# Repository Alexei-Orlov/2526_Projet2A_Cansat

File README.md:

# 🛰️ CanSat 2025-2026
   
> **ENSEA's CanSat team project for the 2025–2026 C'Space edition**

We are a team of second-year engineering students at ENSEA taking part in the 2025–2026 edition of the CanSat competition. CanSat competitions challenge teams to design, build and launch a can-sized (33 cl) satellite that carries out scientific or engineering missions during its descent.

This year's missions are listed below:

- **Main Mission (Mandatory)**
   - **Mission 1: Deployment and Landing**
       - **Integration**: The CanSat must be equipped with a parachute stowed inside the device, designed to deploy during flight.
       - **Deployment**: The CanSat must successfully deploy its parachute at an altitude between 75 and 90 meters.

- **Secondary Missions (Optional)**
    - **Mission 2: Downsizing**
    **Reducing** the CanSat to a 33 cl format doubles the team's score on the technical section.

    - **Mission 3: Ground Study**
    Conduct a study of a topographical feature during the flight.

    - **Mission 4: Onboard Camera**
    Record a video of the parachute deployment or of the CanSat's landing.

- **Bonus Mission**
    - During the descent or after landing, the CanSat may perform an additional mission. Its evaluation is at the jury's discretion, and it must be validated by the controllers during RCE1 to ensure compliance with the rules.

And finally, here is the list of team members and their roles:

| Name | Role |
|------|------|
| Alexeï DOUILLARD | 3D Modeling, Satellite integration, PCB |
| Juan Pablo BARONA CIFUENTES | Embedded systems, firmware |
| Ted KOYAZANDE | Ground Station, Communications |
| Amr TAOUIS | PCB Design and testing |
| Abdelmoughit HAJJI LAAMOURI | Code |

---

## 📋 Table of Contents

- [Objectives](#-objectives)
- [Project Structure](#-project-structure)
- [Development](#-development)
  - [Block diagram of the solution](#-block-diagram-of-the-solution)
  - [Used components description](#-used-components-description)
  - [Electronic design](#-electronic-design)
  - [Mechanical design](#%EF%B8%8F-mechanical-design)
  - [RTOS software architecture](#-rtos-software-architecture)
  - [Data acquisition & routing flow](#-data-acquisition--routing-flow)
  - [Communications & software architecture](#-communications--software-architecture)
  - [Ground Station](#-ground-station-mission-control-center)
  - [Telemetry analysis & 3D terrain reconstruction](#-telemetry-analysis--3d-terrain-reconstruction)
  - [Wind tunnel](#-wind-tunnel)
  - [Drone](#%EF%B8%8F-drone)
- [Resources and useful links](#-resources-and-useful-links)
- [Future plans](#-future-plans)

---

## 📋 Objectives

Based on the missions we chose to fulfill among those listed above, we defined the following objectives.

- **Main Mission (Mandatory)**
  - Design a kirigami-inspired drogue chute that also acts as a protective cap on the CanSat and is used to extract the main parachute. The drogue chute is released by a string and an elastic band tied to a servomotor; the whole mechanism is tested in a homemade wind tunnel.

- **Secondary Missions**
  - **Mission 2: Downsizing**
    - Fit everything within the 330 mL / 350 g limits, using a 6-layer PCB and a very lightweight parachute.

  - **Mission 3: Ground study**
    - **Plan A** (currently active):
      Use a 100 m time-of-flight (ToF) LiDAR to map the ground.
      Induce a rotation thanks to a helicoidal-shaped can, so the beam sweeps the terrain in a spiral as the CanSat falls.
      Georeference each measured point using an Inertial Measurement Unit (IMU), a barometer and a GNSS receiver. The wind tunnel is also used to validate that the can shape actually spins.
    - **Plan B**:
      Use a high-resolution camera to film the whole descent and build a topographical map with AI-based reconstruction after the mission.
  - **Mission 4: Onboard Camera**
    - Record the landing using a small self-contained mini camera.
- **Bonus Mission**
  - Stream part of the recorded data to the ground station during the descent, within the transmission rate of our LoRa module.

## 📁 Project Structure

```
2526_Projet2A_Cansat/
│
├── 📖 README.md                     # This file — project overview
├── 📖 README_GUI.md                 # Ground segment & data pipeline documentation
├── 📄 logs.md                       # Session-by-session work log
│
├── 💻 Firmware/satellite_telemetry/
│   ├── Cansat_V1/                   # STM32CubeIDE project — current flight firmware
│   ├── Cansat_V3/                   # Next firmware iteration (in progress)
│   ├── GUI/                         # Ground station application (Raspberry Pi 5, PyQt5)
│   └── Analysis_Tools/              # Legacy analysis scripts (superseded by 3D/)
│
├── 📂 3D/                           # Post-flight analysis & LIDAR point cloud pipeline
│   ├── cloudPoints.py               # 3D terrain point cloud (main tool)
│   ├── distanceDistribution.py      # LIDAR range histogram
│   ├── generate_sample_data.py      # Synthetic test data generator
│   ├── lidar_common.py              # Shared loading / cleaning / georeferencing
│   ├── COMMANDES.txt                # Full CLI reference
│   └── Analysis_Tools/              # Telemetry dashboards & physics analyses
│
├── ⚡ Hardware/
│   ├── PCB/                         # KiCad projects: Mainboard V1/V2/V3, HMI, custom libraries
│   └── 3D_Modeling/                 # Mechanical schematic & STL exports
│
├── 📂 backup data cansat/           # Real SD-card datasets from field tests
├── 🖼️ IMG/                          # Pictures used by the documentation
├── 📂 Documents/                    # SCAE documents, pictures, definition dossier
├── 📂 Reports/                      # Project reports (PDF)
└── 📂 Wind turbine/                 # Wind tunnel documentation & CFD attempt
```

## 🔧 Development

The development section is divided into four parts:
- Block diagram
- Explanation of the components
- Technical sections
- Software used

First, here is the block diagram of the solution, which shows how the project is organized.

### 💡 Block diagram of the solution

<div align="center">
  <br><br>
  
</div>

### 🔗 Used components description

All the blocks shown above are implemented with the components listed below.

| Component | Reference | Description | Justification |
| :--- | :--- | :--- | :--- |
| **LoRa Module** | SX1276 | The SX1276/77/78/79 transceivers feature the LoRa™ long-range modem, providing ultra-long-range spread-spectrum communication and high interference immunity while minimizing current consumption. | Long-range communication was required with a solid, reliable interface; it was also recommended by last year's CanSat team from the school. Mounted on the mainboard PCB. |
| **LiDAR Altimeter** | LW20/C | A compact, IP67-rated laser altimeter from LightWare. It provides high-precision distance measurements up to 100 meters using time-of-flight technology, and supports multiple returns. | Enables accurate terrain mapping for the ground study mission. |
| **Microcontroller (MCU)** | STM32G431CBU6 | A 32-bit ARM Cortex-M4 microcontroller by STMicroelectronics, featuring mixed-signal capabilities, high-speed processing (170 MHz) and hardware mathematical accelerators (CORDIC/FMAC). | High processing speed is required for sensor fusion and real-time control loops, handling data faster and more efficiently than typical beginner boards. |
| **Barometer** | BMP581 | A high-precision absolute barometric pressure sensor designed for mobile applications, offering low noise and low power consumption. | Determines altitude and vertical velocity (descent rate). It is critical for triggering parachute deployment based on pressure changes. Also recommended by last year's team. |
| **IMU (Inertial Measurement Unit)** | BNO055 | A 9-axis System-in-Package integrating a triaxial 14-bit accelerometer, a triaxial 16-bit gyroscope (±2000 °/s) and a triaxial geomagnetic sensor, with a dedicated microcontroller running the sensor fusion. | Provides orientation data (Euler angles, quaternions) directly. The onboard sensor fusion offloads complex math from the main MCU, ensuring accurate attitude estimation. |
| **GNSS Module** | SAM-M10Q | A patch-antenna module from u-blox featuring the M10 standard-precision GNSS platform. It supports concurrent reception of four GNSS constellations (GPS, GLONASS, Galileo and BeiDou). | Required to track the CanSat's trajectory and lateral drift. Concurrent reception ensures a faster time-to-first-fix and better positioning accuracy, and it provides a redundant altitude source. |
| **Voltage Regulator (LDO)** | LDO40LPU33RY | A high-precision, low-dropout voltage regulator from STMicroelectronics providing a stable output with low quiescent current and low noise. | Provides a clean, stable 3.3 V rail to the sensitive electronics (MCU and sensors), filtering out noise coming from the main power rail. |
| **Local Storage** | MicroSD card + Molex 473092651 | A standard high-capacity non-volatile flash storage card interfaced over SPI through the Molex 473092651 card reader. | Stores the full sensor telemetry and the high-rate LiDAR stream with timestamps. This is the data recovered post-flight for analysis and terrain reconstruction. |
| **Single-Board Computer** | Raspberry Pi 5 | A low-cost, credit-card-sized computer running a Linux-based operating system. | Hosts the ground station: it processes the incoming telemetry stream, runs the graphical user interface (GUI) for data visualization and stores the mission logs. |
| **Battery** | 2-cell LiPo (7.4 V), 2 × 500 mAh | A lithium-polymer rechargeable battery pack of two cells in series, providing a nominal 7.4 V and high discharge capability. | The 7.4 V output matches the input range of the voltage regulators, providing enough headroom to maintain stable power throughout the mission. |
| **Buck Converter** | LMR51625 | A wide-input synchronous buck converter from Texas Instruments, designed to step high input voltages down to logic levels with high efficiency in a compact footprint. | Steps the 7.4 V battery voltage down to 5 V efficiently. Unlike a linear regulator, this switching regulator minimizes heat generation and power loss. |
| **JST Connectors** | JST SH vertical | Small board-to-wire connectors, used in 3- to 7-pin variants. Thanks JST for the samples! | All external modules are connected through JST SH connectors — a good compromise between compactness and ease of use. |
| **Camera** | Drone camera | HD camera module salvaged from a drone, with a 2.4 GHz receiver and an SD card reader, powered by a separate 500 mAh 3.4 V battery. | We found two very similar HD cameras from cheap drones; one only works through a Wi-Fi app while the other one is controllable via UART. |

### 🔌 Electronic design
#### Mainboard PCB
The electronic architecture of the Vortex project is based on a reverse-engineering process. By analyzing last year's project — and more precisely last year's PCB — we identified the key points of the design and the components that needed to change. Based on this process, we selected the components listed above to meet the requirements of our missions and drew the schematic.

<div align="center">
  <br><br>
  
</div>

To integrate this large number of components within the restricted 33 cl volume of the can, we developed a 6-layer PCB. The stack-up is organized as follows:
1. Signal
2. GND
3. Signal
4. PWR
5. GND
6. Signal

Here is the final PCB:

<div align="center">
  <br><br>
  <br><br>
  
</div>

And here are the rendered 3D models of the board.

**Front side**: STM32 (center), barometer (top), JTAG connector (top right), IMU (bottom right), SD card reader (bottom left), status LEDs and buttons (left).
There are two oscillators: a 12 MHz clock for the STM32 (to its left) and a 32.768 kHz clock for the IMU (above the IMU).

<div align="center">
  
</div>

**Back side**: VBAT → 5 V buck converter (top left), main 3.3 V LDO (center right) and a second 3.3 V LDO with an enable function for the LoRa module (bottom left). Connectors to the external modules:
- Motor (top left)
- Time-of-flight sensor (top right)
- LoRa module (right)
- HMI — *see next section* (bottom right)
- GNSS (bottom left)
- 7.4 V battery (right)

There are also two power test points: one for the 5 V rail (top left) and one for the main 3.3 V rail (top right).
The remaining test points expose the onboard components (SD card, IMU, barometer); their pinout can be found in the KiCad project.

The motor output turned out not to be necessary, but we kept it as it leaves room to implement new features if needed.

<div align="center">
  
</div>

> ⚠️ **Warning!** The V1 board has a mistake in the buck converter's footprint: we had to rewire it manually so it could power the rest of the mainboard. There is also a mistake in the routing of the switchable 3.3 V rail: the enable-controlled 3.3 V supply was meant to feed the LoRa connector but was mistakenly wired to the GNSS connector.
> Both issues were fixed in V2, and the latest version, V3, is a cleaner design with additional electrical protections.

The V2 and V3 boards are fully functional; however, some rework was needed to bring out the new UART camera pins in place of the original camera-enable pin. The changes concern the ADC of the battery measurement circuit and the HMI button interrupt.

On the picture below (V1 board): the blinking blue LED is driven by the microcontroller, and the red LEDs indicate that the LDOs are running — one is on by default, the other one is enabled by the microcontroller.

<div align="center">
  
</div>

#### HMI PCB
We also developed a secondary HMI (Human-Machine Interface) PCB (2 layers). This board communicates with the mainboard over I2C to drive an onboard status screen. It also carries two addressable LEDs, providing a programmable visual feedback system to monitor the CanSat's state before and during the launch.

<div align="center">
  <br><br>
  <br><br>
  
</div>

The HMI PCB was tested in integration with an OLED screen and a Nucleo development board. The display correctly shows the CanSat system status (LoRa link state, battery level), and the onboard button cycles through the information screens. A short circuit between GND and 3.3 V appeared after re-soldering a loose LED and was resolved. A custom enclosure for the HMI PCB and the OLED screen was designed in Onshape so they fit inside a handheld remote-control casing. The final step for the HMI PCB was to connect it to the mainboard, so the display shows the actual real-time status of the onboard components instead of test values.

<div align="center">
  <br><br>
  <br><br>
  <br><br>
</div>

### ⚙️ Mechanical Design

#### CanSat Core
Our CanSat is split into two independent sections:
- The **upper section** (nicknamed "Pepe") has a spring-loaded triple-fairing opening. The fairing is kept closed by a trigger, which is pulled out by the drogue chutes. To calibrate the altitude at which the trigger is released, we change the number of chained drogue chutes (detailed below).
- The **lower section** (nicknamed "Latz") holds the entire electronics skeleton (nicknamed "Gravitsappa"). It is decoupled from the top by an M5 bearing and carries a spiral running all around the body to induce a spin — this spin is what lets our LiDAR scan the ground in a spiral pattern as the CanSat falls. This is also why the upper section has vertical fins: they prevent the parachute from spinning along.

The mechanical schematic is available [here as a PDF](./Hardware/3D_Modeling/Cansat%20Schematic%20SCAE.pdf) or [here as the Onshape project](https://cad.onshape.com/documents/c1d9fbb7572429731402c7f6/w/9922ef0afe1ea96367c92f22/e/19dd7d98b534d5ce389091af).
<div align="center">
  
</div>
<div align="center">
  
</div>
<table style="width:100%;">
  <tr>
    <td style="text-align:left;">
      
    </td>
    <td style="text-align:center;">
      
    </td>
    <td style="text-align:right;">
      
    </td>
  </tr>
</table>

#### Drogue chutes
The drogue chute is a kirigami-inspired parachute (*see the research paper in the resources section*). We laser-cut these parachutes out of a K-Way jacket, which we found to offer the best compromise between strength and flexibility.

<div align="center">
  
</div>

Example of chained drogue chutes used to increase the pulling force:
<div align="center">
  
</div>

#### Main parachute
The parachute was sized using the fundamental principle of dynamics at steady-state descent velocity (mg = ½ρC_dSV²). Targeting a descent speed between 2 and 5 m/s, we obtained a canopy area of approximately 0.116 m², i.e. a diameter of approximately 0.385 m, and settled on a 45 cm parachute. This choice was discussed with and approved by an aerospace specialist. Our round canopy was purchased from Klima.

<div align="center">
  
</div>

### 🧠 RTOS Software Architecture

To ensure deterministic execution, prevent data starvation and keep the 3D topographical mapping synchronized, the CanSat's flight software is built on **FreeRTOS**. We implemented a **10 Hz unified-snapshot architecture**: sensor data is gathered, fused and dispatched to both the ground station and the onboard SD card simultaneously.

The system is divided into concurrent tasks communicating safely through RTOS queues (`qSensorEvents`, `qLoRa`, `qSDCard`):

#### 🧵 Task Management
- **`TaskFSM` (normal priority):** the brain of the satellite. It evaluates the flight state at 20 Hz, handles the LED visual feedback and acts as the master metronome. Every 100 ms (10 Hz), it requests sensor readings and builds a unified `TelemetryPacket_t` that feeds the communication and storage queues.
- **`TaskSensors` (high priority):** the data gatherer. It processes hardware interrupts and I2C/UART streams to extract data from the BMP581 (barometer with thermal feed-forward compensation), the BNO055 (Euler angles, quaternions and gyro), the LW20/C (LiDAR distance) and the SAM-M10Q (background NMEA parsing).
- **`TaskLoRa` (low priority):** the communicator. It serializes the unified telemetry struct into our custom **v2.4** comma-separated protocol and transmits it through the SX1276 module. It also handles standby broadcasts and the guaranteed-delivery calibration handshake.
- **`TaskSDCard` (low priority):** the data logger. It uses the **FATFS** library over a custom low-level SPI driver to mount a MicroSD card and log the flight into two CSV files per session (`DATA_xxx.CSV` at 10 Hz, `LIDA_xxx.CSV` at up to 50 Hz). To prevent hardware bottlenecks during high-speed laser mapping, it batches `f_sync()` calls, safely committing the data to the flash without stalling the RTOS.
- **`TaskHMI`:** drives the OLED status screen and the configuration button of the HMI PCB.

#### 🔄 Finite State Machine (FSM)
The CanSat operates fully autonomously. Flight states are evaluated dynamically from environmental triggers detected by the sensor fusion (primarily combining the LiDAR and the barometer).

<div align="center">
   
</div>

<br>

| State | Name | Description | In Transition | Out Transition | Power Supply | LIDAR | Barometer | GNSS | LoRa | IMU |
| :---: | :--- | :--- | :--- | :--- | :---: | :---: | :---: | :---: | :---: | :---: |
| **OFF** | Off state | The power switch is OFF; nothing is powered. | `powerSwitch = 0` | `powerSwitch = 1` | 🔴 OFF | 🔴 OFF | 🔴 OFF | 🔴 OFF | 🔴 OFF | 🔴 OFF |
| **S0** | Standby | Idle mode, waiting for configuration. Low consumption. | `powerSwitch = 1` | `conFlag = 1` | 🟢 ON | 🔴 OFF | 🟢 ON | 🟢 ON | 🔴 OFF | 🔴 OFF |
| **S1** | Config | Configuration mode entered when the status interface is connected. Exits when unplugged. | `conFlag = 1` | `conFlag = 0` | 🟢 ON | 🟢 ON | 🟢 ON | 🟢 ON | 🟢 ON | 🟢 ON |
| **S2** | Ready | Waiting for the ascent (or a return to configuration). | `conFlag = 0` | `lidar = 0` and `height > 5` | 🟢 ON | 🟢 ON (Low Power) | 🟢 ON | 🟢 ON | 🟢 ON | 🟢 ON |
| **S3** | Ascension | Ascent phase; the device waits for the drop. | `lidar = 0` and `height > 5` | `lidar = 1` and `height > 5` | 🟢 ON | 🟢 ON (Low Power) | 🟢 ON | 🟢 ON | 🟢 ON | 🟢 ON |
| **S4** | Drop | Descent phase; all sensors are ON. High consumption. | `lidar = 1` and `height > 5` | `height < 5` | 🟢 ON | 🟢 ON | 🟢 ON | 🟢 ON | 🟢 ON | 🟢 ON |
| **S5** | Recovery | Final steady state, waiting for recovery and data extraction. | `height < 5` | `powerSwitch = 0` | 🟢 ON | 🔴 OFF | 🔴 OFF | 🟢 ON | 🟢 ON | 🔴 OFF |

In the implementation, every transition is **debounced**: the triggering condition must hold for a fixed window (1–3 s at 20 Hz depending on the transition) with only a few outlier samples tolerated, which makes the FSM robust to isolated noisy readings.

### 📊 Data Acquisition & Routing Flow

The CanSat's data pipeline is designed to be asynchronous, modular and highly reliable. Data is gathered from four distinct sensors across different communication buses, packaged into independent C structures, and finally routed to the two storage and transmission endpoints.

Here is the breakdown of the data acquisition architecture:

#### 1. Sensor Inputs & Protocols
The system continuously listens to four hardware interfaces:
* **GNSS (UART):** receives continuous NMEA frames from the satellites (10 Hz fix rate).
* **Barometer (I2C):** polled for high-precision atmospheric pressure and temperature.
* **IMU (I2C):** read by DMA for the onboard sensor-fused orientation and acceleration.
* **LIDAR (UART):** receives high-speed distance measurements from time-of-flight laser pulses (up to 50 Hz).

#### 2. Data Encapsulation (The Structs)
To keep the data organized and synchronized, each sensor's readings are immediately packed into a dedicated `struct`. Every struct includes a **timestamp** captured at the exact millisecond the data was read, ensuring proper synchronization for post-flight analysis.

* **GNSS struct:** `timestamp`, `latitude`, `longitude`, `altitude`, `satellites`
* **Barometer struct:** `timestamp`, `height`, `temperature`
* **IMU struct:** `timestamp`, `head` (yaw), `pitch`, `roll`, `accelX`, `accelY`, `accelZ`
* **LIDAR struct:** `timestamp`, `distance`

#### 3. Data Destinations
Once the individual structures are populated, the FSM gathers them into a single unified master packet (`TelemetryPacket_t`). This unified snapshot is then dispatched simultaneously to two endpoints:

* 📡 **LoRa module:** the data is serialized into a comma-separated string (our custom **v2.4** protocol) and broadcast over the air at a 10 Hz dispatch rate to the Python ground station for real-time monitoring.
* 💾 **SD card:** the same data is routed to the onboard FATFS SD card over SPI. It is logged as CSV files and committed to the physical flash (`f_sync`) continuously, ensuring no data is lost on impact. The high-rate LiDAR stream gets its own file (`LIDA_xxx.CSV`, with quaternion attitude and GNSS altitude) to feed the 3D terrain reconstruction.

### 📡 Communications & Software Architecture

The software and communication architecture of the Vortex project was developed with a primary focus on data integrity and link stability, treating the telemetry stream as the mission's critical lifeline. Following a reverse-engineering analysis of the previous team's communication structure, we chose to rebuild the data transmission system to improve packet efficiency and error handling. The solution is implemented with the SX1276 module described above. To ensure the reliability of the received data, we integrated a Cyclic Redundancy Check (CRC) mechanism, which validates packet integrity before parsing begins at the ground station.

On the navigation front, the software driver for the SAM-M10Q GNSS module parses specific NMEA frames (GNGGA, GNGSA and GNRMC) to extract 3D position, velocity and satellite data. We used the u-center 2 software for the initial configuration, enabling SBAS/EGNOS support to maximize positioning accuracy. Testing was iterative, moving from indoor functional verification to long-range outdoor link tests to validate the link budget.

- **Summary**

  - **Robust LoRa Protocol**
    - **Error handling:** CRC (Cyclic Redundancy Check) and header validation automatically discard corrupted frames at the ground station.
    - **Handshaking:** a connection verification sequence ("CANSAT OK") confirms receiver readiness before mission start.

- **Advanced GNSS Integration**
  - **NMEA parsing:** the STM32 parses specific NMEA sentences:
    - **GNGGA:** global position (latitude, longitude, altitude)
    - **GNRMC:** recommended minimum navigation information
    - **GNGSA:** DOP and active satellites
  - **Accuracy optimization:** SBAS/EGNOS support activated via u-center 2 to improve vertical and horizontal precision; the GNSS altitude is also logged (`gnss_alt`) as a redundant altitude source for post-flight processing.

- **Testing & Validation**
  - **GNSS precision:** comparative tests between indoor (cold start) and outdoor environments to characterize time-to-first-fix and coordinate stability — outdoor performance is clearly better.
  - **Range testing:** line-of-sight (LoS) tests between the CanSat emitter and the ground station receiver to validate the LoRa link budget and antenna performance at distance.

**Current status:** the IMU values are integrated in the main telemetry stream; the full pipeline (sensors → LoRa/SD → analysis) has been validated during field tests.

### 🧰 Ground Station (Mission Control Center)

<div align="center">
  
</div>

The Ground Station serves as the mission's central command and telemetry hub, engineered for high-performance data acquisition and real-time situational awareness. It is a portable, ruggedized unit built around a **Raspberry Pi 5** single-board computer.

#### **Communication & Data Link**
The station uses a **LoRa SX1276** transceiver operating at **869.53 MHz**. The link is governed by our custom **v2.4 telemetry protocol**, processing 17-field packets that carry the IMU data, GNSS coordinates, atmospheric conditions, flight phase flags and battery voltage. To ensure data integrity, the system implements hardware-level SPI communication and software-side CSV export for redundant storage.

#### **Real-Time Visualization Suite**
The ground station software is an asynchronous, multi-threaded **PyQt5** application designed for low-latency monitoring:
* **3D kinematic rendering**: uses **PyOpenGL** to visualize the satellite's orientation in real time, mapping the incoming Euler angles onto a custom STL model.
* **Dynamic geospatial tracking**: features an optimized **OpenStreetMap (OSM)** tile map engine that handles position updates in under 1 ms thanks to pre-fetched in-memory tile caching.
* **Telemetry analytics**: real-time plotting via **PyQtGraph**, deriving metrics such as vertical speed and applying a 12-sample moving average to smooth the battery voltage.
* **Mission state monitoring**: real-time flight phase indicators (Go for launch, Ascension, Drop, Recovery) decoded from the telemetry bitmask.

Detailed specifications regarding the software architecture, the SX127x configuration, the onboard logging scheme and the post-flight processing pipeline can be found in **[README_GUI.md](./README_GUI.md)**.

### 📈 Telemetry Analysis & 3D Terrain Reconstruction

All post-flight processing lives in the **[3D/](./3D/)** folder and operates on the two CSV files recovered from the SD card after each flight (`DATA_xxx.CSV` for the telemetry, `LIDA_xxx.CSV` for the LiDAR stream).

#### Telemetry analysis suite
- **`Analysis_Tools/Basic/analyze_telemetry.py`** — a 10-panel flight dashboard (accelerometer, gyroscope, orientation, temperature, altitude, vertical speed, GPS, battery), with per-phase color bands and a text report of the flight statistics.
- **`Analysis_Tools/Advanced/advanced_analysis.py`** — rotation/tumbling analysis, GPS trajectory, energy budget, automatic anomaly detection (data gaps, GPS jumps, accelerometer saturation, temperature spikes) and a Google Earth KML export.
- **`Analysis_Tools/Advanced/advanced_features.py`** — physics-based analyses: drag coefficient estimation, parachute deployment detection (vertical jerk) and battery consumption per flight phase.

#### 3D point cloud pipeline (Mission 3)
The spiral LiDAR scan is turned into a georeferenced 3D point cloud of the overflown terrain:
- **`cloudPoints.py`** fuses each range sample with the logged attitude (quaternions, SLERP-interpolated between IMU bursts) and position (GNSS + barometric or GNSS altitude), producing an interactive 3D view and optional `.xyz` exports for CloudCompare.
- **`distanceDistribution.py`** provides a quick histogram sanity check of the measured ranges.
- **`generate_sample_data.py`** generates synthetic flight data so the pipeline can be developed and tested without a launch.

The complete command-line reference is kept in [`3D/COMMANDES.txt`](./3D/COMMANDES.txt), and the full pipeline documentation is in **[README_GUI.md](./README_GUI.md)**.

#### Field test data
Real SD-card datasets recorded during our test campaigns are archived in [`backup data cansat/`](./backup%20data%20cansat/), including a 1-hour endurance test, car-drive tests and building-tour scans used to validate the LiDAR georeferencing.

### 🍃 Wind Tunnel

To test the parachutes reliably, we built a wind tunnel powered by two 350 W counter-rotating brushless drone motors. The counter-rotation ensures no unwanted swirl is induced in the flow.

<div align="center">
  
</div>

We use a servo-motor tester as the speed control (it works with both servos and brushless ESCs) and check the airspeed with an anemometer.

The device is powered by a 12 V, 30 A power supply housed in a PLA enclosure. Even without running the motors at full power, the tunnel produces a 60 km/h wind, which is more than our CanSat should reach before deployment.

<div align="center">

</div>

A single-fan test:

<div align="center">
  
</div>

The motor hub was covered with an aerospike-inspired nozzle in an attempt to preserve some of the airflow going around it:
<div align="center">
  
</div>

#### Precautions before use
Before operating the wind tunnel, check that the propellers are clear and that nothing can get sucked in, then plug in the power supply and turn it on (also check that the emergency stop is not engaged). The servo tester knob must be set to 0; once the ESC has emitted its three beeps, the wind tunnel is armed and ready to operate.

### ✈️ Drone

We carried out early mechanical drop tests with a heavy-duty drone that a professor kindly let us use, and we plan to build our own to run more tests.

Here is the drop mechanism:
<div align="center">
  
</div>

## 📚 Resources and useful links

### 👾 Software used

- u-center 2 — GNSS configuration
- LightWare Studio — LIDAR
- STM32CubeIDE v1.19.0 — STM32 firmware
- KiCad — PCB design
- Onshape — 3D modeling

### 🔗 Links

- [Previous ENSEA CanSat GitHub](https://github.com/mathieupommery/CANSAT_ARES_ENSEA)
- [Onshape folder](https://cad.onshape.com/documents?resourceType=folder&nodeId=558406456f078be48d4c722b&column=modifiedAt&sortOrder=asc)
- [Kirigami-inspired parachute (research paper)](https://www.nature.com/articles/s41586-025-09515-9#Fig1)
- [FreeRTOS guide](https://www.youtube.com/watch?v=OPrcpbKNSjU)
---

### 🚀 Future plans
The next steps are:

- Improve the deployment reliability
- Finalize the Cansat_V3 firmware iteration (barometer safety net, higher GNSS sample rate)
- Run more drone drop tests and validate the point cloud pipeline on real flight data

Given the current state of progress, we expect to complete the project on time with all of the missions fulfilled.

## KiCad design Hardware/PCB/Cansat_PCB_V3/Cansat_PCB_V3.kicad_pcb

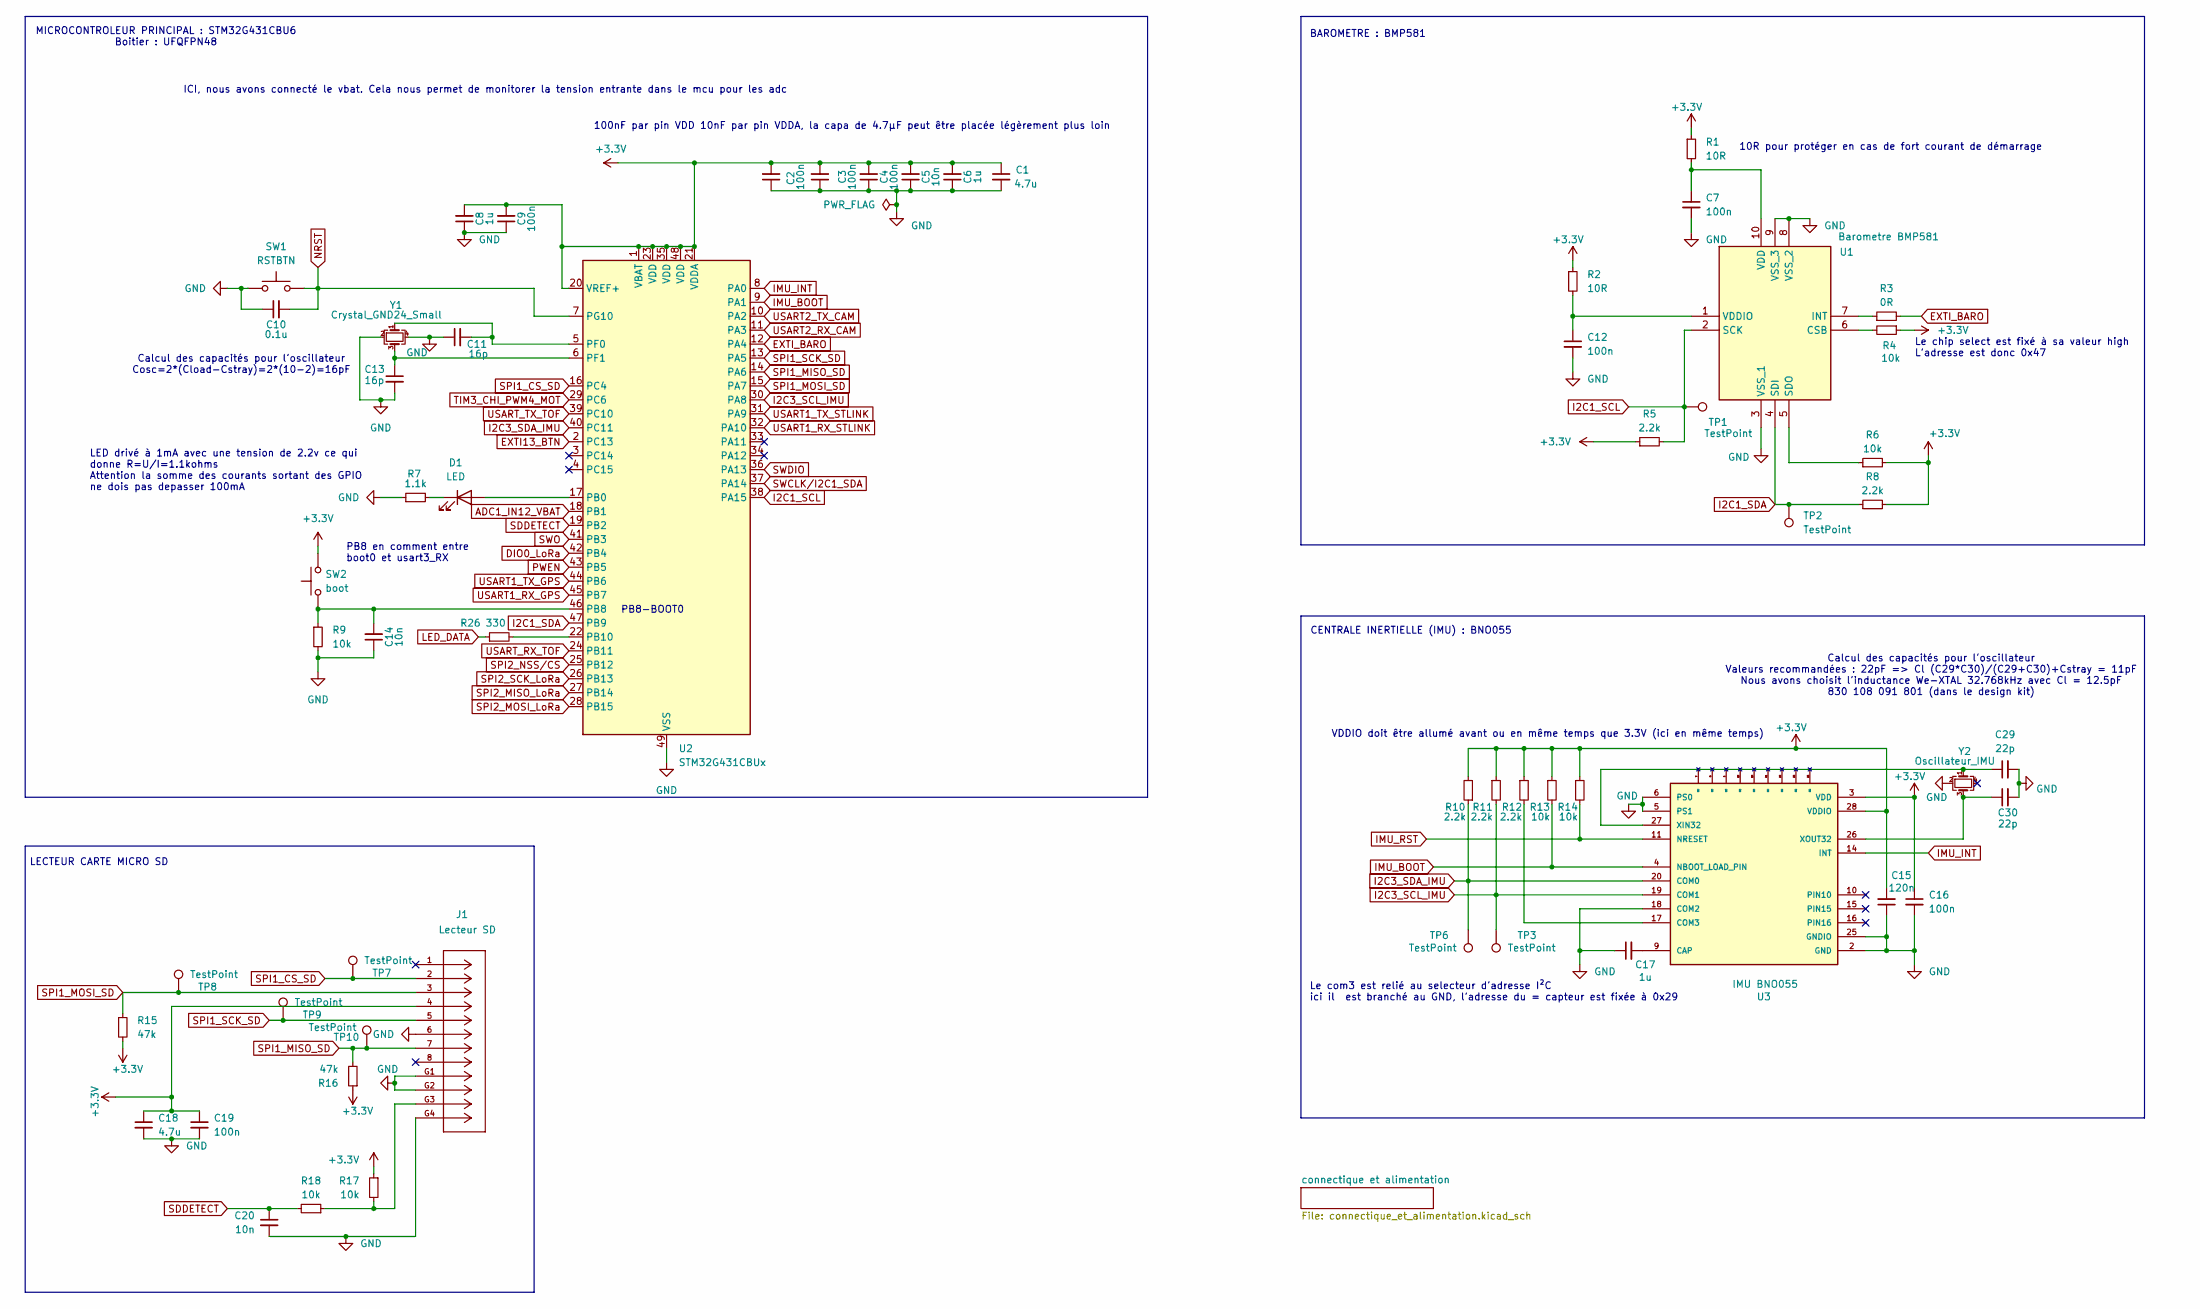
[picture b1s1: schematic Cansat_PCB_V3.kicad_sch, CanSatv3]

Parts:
C1, C18: 4.7u; C_0402_1005Metric_Pad0.74x0.62mm_HandSolder
C2, C3, C4, C7, C9, C12, C16, C19: 100n; C_0402_1005Metric_Pad0.74x0.62mm_HandSolder
C5, C14, C20: 10n; C_0402_1005Metric_Pad0.74x0.62mm_HandSolder
C6, C8, C17: 1u; C_0402_1005Metric_Pad0.74x0.62mm_HandSolder
C10: 0.1u; C_0402_1005Metric_Pad0.74x0.62mm_HandSolder
C11, C13: 16p; C_0402_1005Metric_Pad0.74x0.62mm_HandSolder
C15: 120n; C_0402_1005Metric_Pad0.74x0.62mm_HandSolder
C29, C30: 22p; C_0402_1005Metric_Pad0.74x0.62mm_HandSolder
D1: LED; LED_0603_1608Metric_Pad1.05x0.95mm_HandSolder
J1: Lecteur SD; CONN12_47309-2651_MOL; Manufacturer_Part_Number 47309-2651
R1, R2: 10R; R_0402_1005Metric_Pad0.72x0.64mm_HandSolder
R3: 0R; R_0402_1005Metric_Pad0.72x0.64mm_HandSolder
R4, R6, R9, R13, R14, R17, R18: 10k; R_0402_1005Metric_Pad0.72x0.64mm_HandSolder
R5, R8, R10, R11, R12: 2.2k; R_0402_1005Metric_Pad0.72x0.64mm_HandSolder
R7: 1.1k; R_0402_1005Metric_Pad0.72x0.64mm_HandSolder
R15, R16: 47k; R_0402_1005Metric_Pad0.72x0.64mm_HandSolder
R26: 330; R_0402_1005Metric_Pad0.72x0.64mm_HandSolder
SW1: RSTBTN; KXT 321 LHS_CNK
SW2: boot; KXT 321 LHS_CNK
TP1, TP2, TP3, TP6, TP7, TP8, TP9, TP10: TestPoint; TestPoint_Pad_D1.0mm
U1: Barometre BMP581; BMP581; Manufacturer_Part_Number BMP581; Mouser Part Number 262-BMP581
U2: STM32G431CBUx; QFN-48-1EP_7x7mm_P0.5mm_EP5.6x5.6mm
U3: IMU BNO055; LGA28R50P4X10_380X520X100; Manufacturer_Part_Number BNO055; Mouser Part Number 262-BNO055
Y1: Crystal_GND24_Small; Crystal_SMD_3225-4pin_3.2x2.5mm
Y2: Oscillateur_IMU; WE-XTAL_IQXC-146

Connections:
+3.3V: C1.1, C2.2, C3.2, C4.2, C5.2, C6.2, C8.2, C9.2, C15.2, C16.1, C18.1, C19.1, J1.4, R1.1, R2.1, R4.1, R5.1, R6.2, R8.2, R10.2, R11.1, R12.1, R13.1, R14.1, R15.2, R16.1, R17.1, SW2.2, U2.1 (VBAT), U2.20 (VREF+), U2.21 (VDDA), U2.23 (VDD), U2.35 (VDD), U2.48 (VDD), U3.3 (VDD), U3.28 (VDDIO); also elsewhere on the board
ADC1_IN12_VBAT: U2.18 (PB1); also elsewhere on the board
DIO0_LoRa: U2.42 (PB4); also elsewhere on the board
EXTI13_BTN: U2.2 (PC13); also elsewhere on the board
EXTI_BARO: R3.2, U2.12 (PA4)
GND: C1.2, C2.1, C3.1, C4.1, C5.1, C6.1, C7.2, C8.1, C9.1, C10.1, C11.1, C12.2, C13.2, C14.1, C15.1, C16.2, C17.1, C18.2, C19.2, C20.2, C29.2, C30.2, J1.6, J1.G1, J1.G2, J1.G4, R7.1, R9.2, SW1.1, U1.3 (VSS_1), U1.8 (VSS_2), U1.9 (VSS_3), U2.49 (VSS), U3.2 (GND), U3.5 (PS1), U3.6 (PS0), U3.18 (COM2), U3.25 (GNDIO), Y1.2, Y1.4, Y2.2; also elsewhere on the board
I2C1_SCL: R5.2, TP1.1, U1.2 (SCK), U2.38 (PA15); also elsewhere on the board
I2C1_SDA: R8.1, TP2.1, U1.4 (SDI), U2.47 (PB9); also elsewhere on the board
I2C3_SCL_IMU: R11.2, TP3.1, U2.30 (PA8), U3.19 (COM1)
I2C3_SDA_IMU: R10.1, TP6.1, U2.40 (PC11), U3.20 (COM0)
IMU_BOOT: R13.2, U2.9 (PA1), U3.4 (NBOOT_LOAD_PIN)
IMU_INT: U2.8 (PA0), U3.14 (INT)
IMU_RST: R14.2, U3.11 (NRESET)
LED_DATA: R26.1; also elsewhere on the board
NRST: C10.2, SW1.2, U2.7 (PG10); also elsewhere on the board
unnamed: D1.2 (A), U2.17 (PB0)
unnamed: D1.1 (K), R7.2
unnamed: J1.G3, R17.2, R18.1
unnamed: R4.2, U1.6 (CSB)
unnamed: R3.1, U1.7 (INT)
unnamed: R6.1, U1.5 (SDO)
unnamed: C7.1, R1.2, U1.10 (VDD)
unnamed: C12.1, R2.2, U1.1 (VDDIO)
unnamed: C14.2, R9.1, SW2.1, U2.46 (PB8)
unnamed: R26.2, U2.22 (PB10)
unnamed: C11.2, U2.5 (PF0), Y1.1
unnamed: C13.1, U2.6 (PF1), Y1.3
unnamed: C17.2, U3.9 (CAP)
unnamed: R12.2, U3.17 (COM3)
unnamed: C29.1, U3.27 (XIN32), Y2.1
unnamed: C30.1, U3.26 (XOUT32), Y2.3
PWEN: U2.43 (PB5); also elsewhere on the board
SDDETECT: C20.1, R18.2, U2.19 (PB2)
SPI1_CS_SD: J1.2, TP7.1, U2.16 (PC4)
SPI1_MISO_SD: J1.7, R16.2, TP10.1, U2.14 (PA6)
SPI1_MOSI_SD: J1.3, R15.1, TP8.1, U2.15 (PA7)
SPI1_SCK_SD: J1.5, TP9.1, U2.13 (PA5)
SPI2_MISO_LoRa: U2.27 (PB14); also elsewhere on the board
SPI2_MOSI_LoRa: U2.28 (PB15); also elsewhere on the board
SPI2_NSS/CS: U2.25 (PB12); also elsewhere on the board
SPI2_SCK_LoRa: U2.26 (PB13); also elsewhere on the board
SWCLK/I2C1_SDA: U2.37 (PA14); also elsewhere on the board
SWDIO: U2.36 (PA13); also elsewhere on the board
SWO: U2.41 (PB3); also elsewhere on the board
TIM3_CHI_PWM4_MOT: U2.29 (PC6); also elsewhere on the board
USART1_RX_GPS: U2.45 (PB7); also elsewhere on the board
USART1_RX_STLINK: U2.32 (PA10); also elsewhere on the board
USART1_TX_GPS: U2.44 (PB6); also elsewhere on the board
USART1_TX_STLINK: U2.31 (PA9); also elsewhere on the board
USART2_RX_CAM: U2.11 (PA3); also elsewhere on the board
USART2_TX_CAM: U2.10 (PA2); also elsewhere on the board
USART_RX_TOF: U2.24 (PB11); also elsewhere on the board
USART_TX_TOF: U2.39 (PC10); also elsewhere on the board

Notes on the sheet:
BAROMETRE : BMP581
100nF par pin VDD 10nF par pin VDDA, la capa de 4.7µF peut être placée légèrement plus loin
Le com3 est relié au selecteur d'adresse I²C ici il est branché au GND, l'adresse du = capteur est fixée à 0x29
Calcul des capacités pour l'oscillateur Cosc=2*(Cload-Cstray)=2*(10-2)=16pF
10R pour protéger en cas de fort courant de démarrage
Le chip select est fixé à sa valeur high L'adresse est donc 0x47
VDDIO doit être allumé avant ou en même temps que 3.3V (ici en même temps)
Calcul des capacités pour l'oscillateur Valeurs recommandées : 22pF => Cl (C29*C30)/(C29+C30)+Cstray = 11pF Nous avons choisit l'inductance We-XTAL 32.768kHz avec Cl = 12.5pF 830 108 091 801 (dans le design kit)
MICROCONTROLEUR PRINCIPAL : STM32G431CBU6 Boitier : UFQFPN48
CENTRALE INERTIELLE (IMU) : BNO055
PB8-BOOT0
PB8 en comment entre boot0 et usart3_RX
ICI, nous avons connecté le vbat. Cela nous permet de monitorer la tension entrante dans le mcu pour les adc
LED drivé à 1mA avec une tension de 2.2v ce qui donne R=U/I=1.1kohms Attention la somme des courants sortant des GPIO ne dois pas depasser 100mA
LECTEUR CARTE MICRO SD

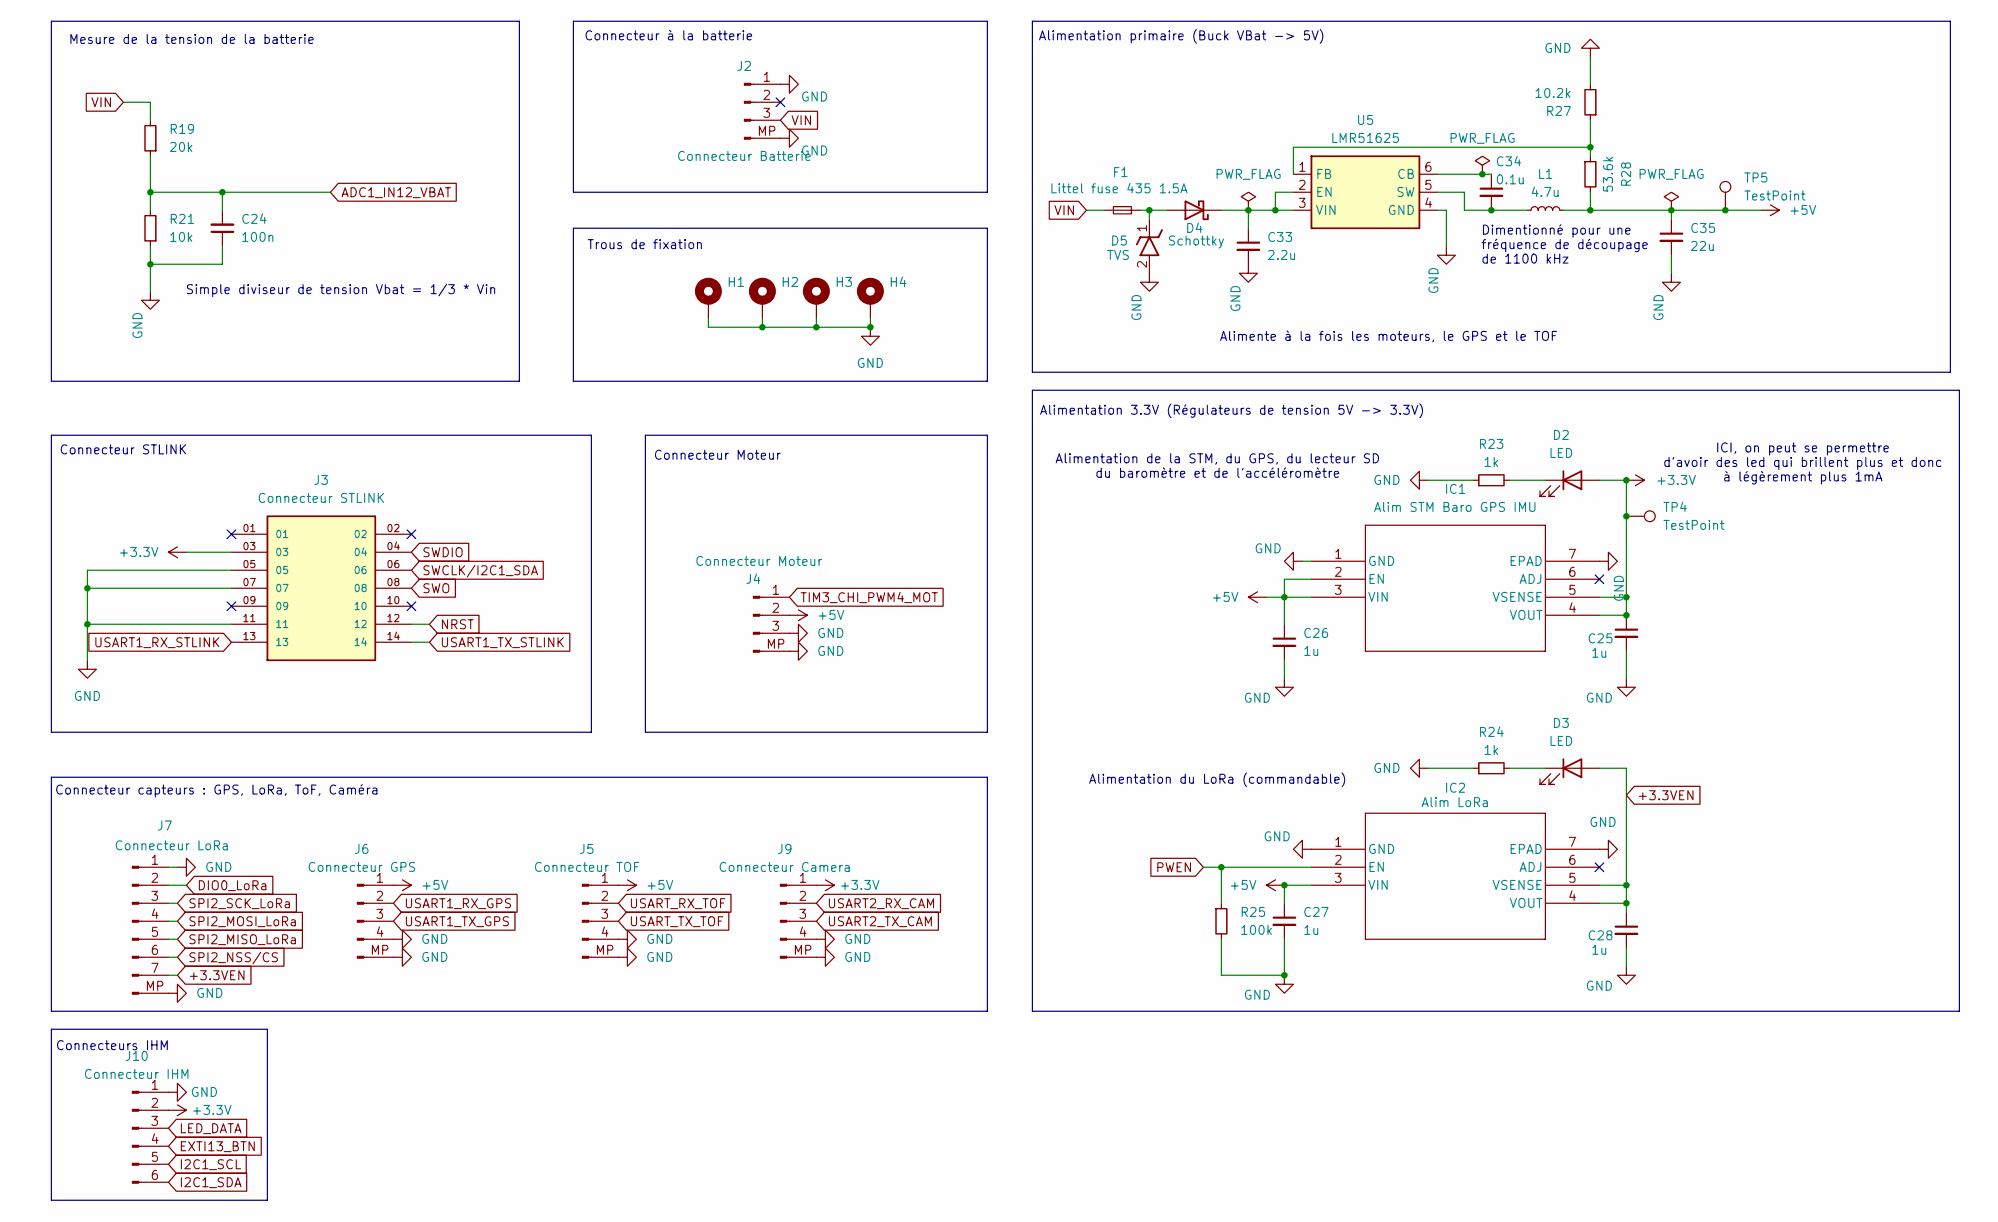
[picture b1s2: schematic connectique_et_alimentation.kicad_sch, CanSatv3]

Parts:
C24: 100n; C_0402_1005Metric_Pad0.74x0.62mm_HandSolder
C25, C26, C27, C28: 1u; C_0402_1005Metric_Pad0.74x0.62mm_HandSolder
C33: 2.2u; C_0402_1005Metric_Pad0.74x0.62mm_HandSolder
C34: 0.1u; C_0402_1005Metric_Pad0.74x0.62mm_HandSolder
C35: 22u; C_0805_2012Metric_Pad1.18x1.45mm_HandSolder
D2, D3: LED; LED_0603_1608Metric_Pad1.05x0.95mm_HandSolder
D4: Schottky; D_SOD-882D
D5: TVS; SPHV12-01ETG; Manufacturer_Part_Number SPHV12-01ETG
F1: Littel fuse 435 1.5A; FUSC1608X43N
H1, H2, H3, H4: MountingHole_Pad; MountingHole_2.2mm_M2_ISO7380_Pad
IC1: Alim STM Baro GPS IMU; DFN6_3X3_STM; Manufacturer_Part_Number LDO40LPU33RY; Mouser Part Number 511-LDO40LPU33RY
IC2: Alim LoRa; DFN6_3X3_STM; Manufacturer_Part_Number LDO40LPU33RY; Mouser Part Number 511-LDO40LPU33RY
J2: Connecteur Batterie; JST_SH_BM03B-SRSS-TB_1x03-1MP_P1.00mm_Vertical
J3: Connecteur STLINK; FTSH-107-XX-YYY-DV-K; PARTREV H
J4: Connecteur Moteur; JST_SH_BM03B-SRSS-TB_1x03-1MP_P1.00mm_Vertical
J5: Connecteur TOF; JST_SH_BM04B-SRSS-TB_1x04-1MP_P1.00mm_Vertical
J6: Connecteur GPS; JST_SH_BM04B-SRSS-TB_1x04-1MP_P1.00mm_Vertical
J7: Connecteur LoRa; JST_SH_BM07B-SRSS-TB_1x07-1MP_P1.00mm_Vertical
J9: Connecteur Camera; JST_SH_BM04B-SRSS-TB_1x04-1MP_P1.00mm_Vertical
J10: Connecteur IHM; JST_SH_BM06B-SRSS-TB_1x06-1MP_P1.00mm_Vertical
L1: 4.7u; IND_WE-MAPI_4020_WRE
R19: 20k; R_0402_1005Metric_Pad0.72x0.64mm_HandSolder
R21: 10k; R_0402_1005Metric_Pad0.72x0.64mm_HandSolder
R23, R24: 1k; R_0402_1005Metric_Pad0.72x0.64mm_HandSolder
R25: 100k; R_0402_1005Metric_Pad0.72x0.64mm_HandSolder
R27: 10.2k; R_0402_1005Metric_Pad0.72x0.64mm_HandSolder
R28: 53.6k; R_0402_1005Metric_Pad0.72x0.64mm_HandSolder
TP4, TP5: TestPoint; TestPoint_Pad_1.5x1.5mm
U5: LMR51625; SOT-23-6

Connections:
+3.3V: C25.1, D2.2 (A), IC1.4 (VOUT), IC1.5 (VSENSE), J3.03, J9.1, J10.2, TP4.1; also elsewhere on the board
+3.3VEN: C28.1, D3.2 (A), IC2.4 (VOUT), IC2.5 (VSENSE), J7.7
+5V: C26.1, C27.1, C35.1, IC1.2 (EN), IC1.3 (VIN), IC2.3 (VIN), J4.2, J5.1, J6.1, L1.2, R28.2, TP5.1
ADC1_IN12_VBAT: C24.2, R19.1, R21.2; also elsewhere on the board
DIO0_LoRa: J7.2; also elsewhere on the board
EXTI13_BTN: J10.4; also elsewhere on the board
GND: C24.1, C25.2, C26.2, C27.2, C28.2, C33.2, C35.2, D5.2 (A), H1.1, H2.1, H3.1, H4.1, IC1.1 (GND), IC1.7 (EPAD), IC2.1 (GND), IC2.7 (EPAD), J2.1, J2.MP, J3.05, J3.07, J3.11, J4.3, J4.MP, J5.4, J5.MP, J6.4, J6.MP, J7.1, J7.MP, J9.4, J9.MP, J10.1, R21.1, R23.1, R24.1, R25.2, R27.2, U5.4 (GND); also elsewhere on the board
I2C1_SCL: J10.5; also elsewhere on the board
I2C1_SDA: J10.6; also elsewhere on the board
LED_DATA: J10.3; also elsewhere on the board
NRST: J3.12; also elsewhere on the board
unnamed: D2.1 (K), R23.2
unnamed: D3.1 (K), R24.2
unnamed: D4.2 (A), D5.1 (K), F1.2
unnamed: C33.1, D4.1 (K), U5.2 (EN), U5.3 (VIN)
unnamed: C34.1, U5.6 (CB)
unnamed: R27.1, R28.1, U5.1 (FB)
unnamed: C34.2, L1.1, U5.5 (SW)
PWEN: IC2.2 (EN), R25.1; also elsewhere on the board
SPI2_MISO_LoRa: J7.5; also elsewhere on the board
SPI2_MOSI_LoRa: J7.4; also elsewhere on the board
SPI2_NSS/CS: J7.6; also elsewhere on the board
SPI2_SCK_LoRa: J7.3; also elsewhere on the board
SWCLK/I2C1_SDA: J3.06; also elsewhere on the board
SWDIO: J3.04; also elsewhere on the board
SWO: J3.08; also elsewhere on the board
TIM3_CHI_PWM4_MOT: J4.1; also elsewhere on the board
USART1_RX_GPS: J6.2; also elsewhere on the board
USART1_RX_STLINK: J3.13; also elsewhere on the board
USART1_TX_GPS: J6.3; also elsewhere on the board
USART1_TX_STLINK: J3.14; also elsewhere on the board
USART2_RX_CAM: J9.2; also elsewhere on the board
USART2_TX_CAM: J9.3; also elsewhere on the board
USART_RX_TOF: J5.2; also elsewhere on the board
USART_TX_TOF: J5.3; also elsewhere on the board
VIN: F1.1, J2.3, R19.2

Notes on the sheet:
Alimentation de la STM, du GPS, du lecteur SD du baromètre et de l'accéléromètre
Alimentation du LoRa (commandable)
Trous de fixation
Alimente à la fois les moteurs, le GPS et le TOF
Connecteur capteurs : GPS, LoRa, ToF, Caméra
Simple diviseur de tension Vbat = 1/3 * Vin
Connecteur à la batterie
Dimentionné pour une fréquence de découpage de 1100 kHz
Connecteur Moteur
Mesure de la tension de la batterie
ICI, on peut se permettre d'avoir des led qui brillent plus et donc à légèrement plus 1mA
Connecteurs IHM
Alimentation 3.3V (Régulateurs de tension 5V -> 3.3V)
Connecteur STLINK
Alimentation primaire (Buck VBat -> 5V)

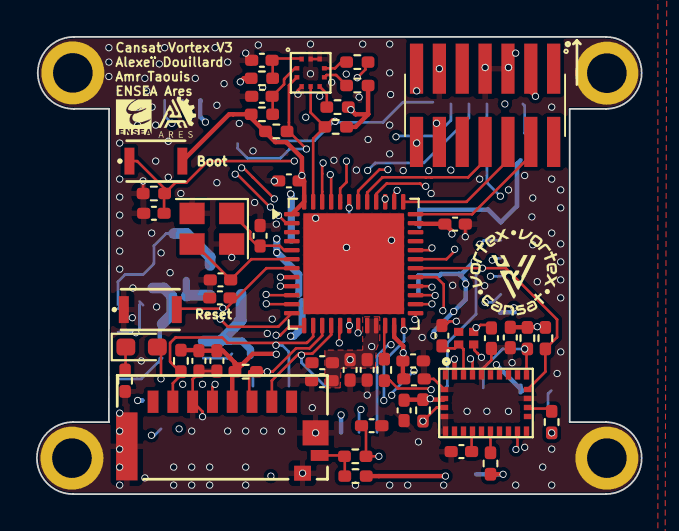
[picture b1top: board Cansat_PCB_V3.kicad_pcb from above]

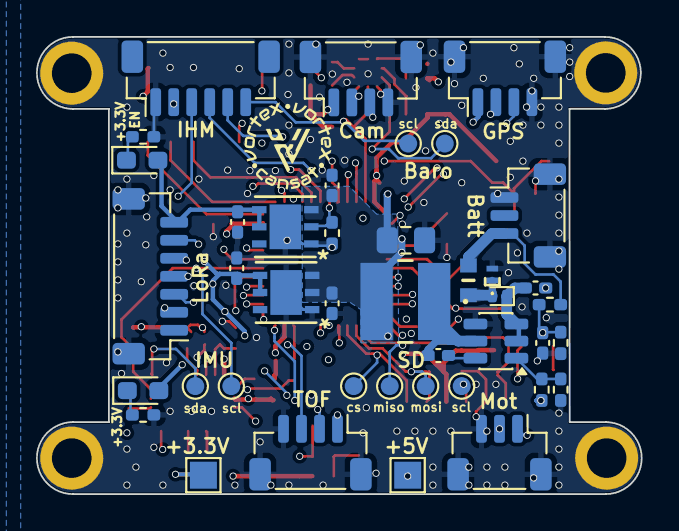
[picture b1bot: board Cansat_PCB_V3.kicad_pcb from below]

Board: 6 copper layers, 33.6 x 25.4 mm, 96 parts (41 on the bottom side), 63 nets.

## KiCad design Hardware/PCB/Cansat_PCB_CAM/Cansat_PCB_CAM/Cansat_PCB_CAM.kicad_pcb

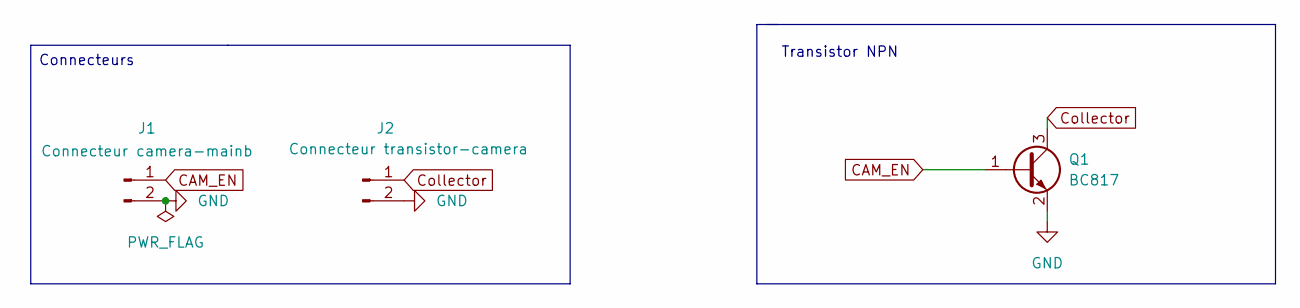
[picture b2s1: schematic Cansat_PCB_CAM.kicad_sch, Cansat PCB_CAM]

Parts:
J1: Connecteur camera-mainb; JST_SH_BM02B-SRSS-TB_1x02-1MP_P1.00mm_Vertical
J2: Connecteur transistor-camera; JST_SH_BM02B-SRSS-TB_1x02-1MP_P1.00mm_Vertical
Q1: BC817; SOT-23

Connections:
CAM_EN: J1.1, Q1.1 (B)
Collector: J2.1, Q1.3 (C)
GND: J1.2, J2.2, Q1.2 (E)

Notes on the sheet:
Transistor NPN
Connecteurs

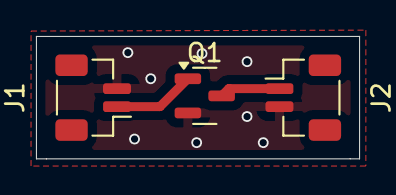
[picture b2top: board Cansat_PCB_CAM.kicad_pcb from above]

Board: 2 copper layers, 18.0 x 6.8 mm, 3 parts (0 on the bottom side), 3 nets.

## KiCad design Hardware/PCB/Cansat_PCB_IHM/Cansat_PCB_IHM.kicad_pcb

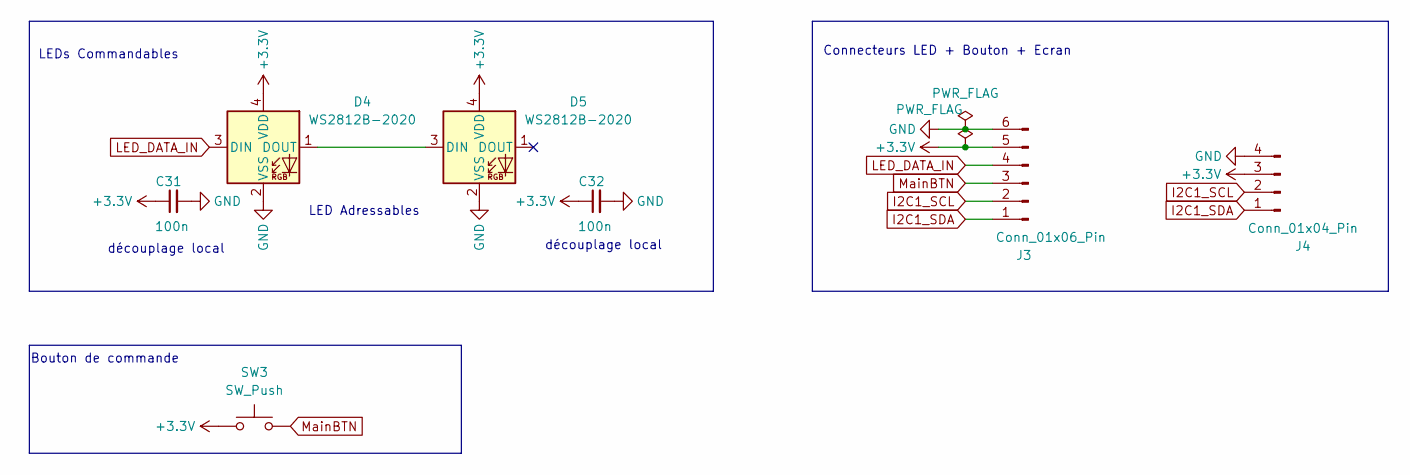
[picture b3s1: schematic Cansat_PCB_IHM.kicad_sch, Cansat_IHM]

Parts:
C31, C32: 100n; C_0402_1005Metric
D4, D5: WS2812B-2020; LED_WS2812B-2020_PLCC4_2.0x2.0mm
J3: Conn_01x06_Pin; JST_SH_BM06B-SRSS-TB_1x06-1MP_P1.00mm_Vertical
J4: Conn_01x04_Pin; JST_SH_BM04B-SRSS-TB_1x04-1MP_P1.00mm_Vertical
SW3: SW_Push; SW_Push_1P1T_NO_CK_PTS125Sx43PSMTR

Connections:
+3.3V: C31.1, C32.1, D4.4 (VDD), D5.4 (VDD), J3.5, J4.3, SW3.1
GND: C31.2, C32.2, D4.2 (VSS), D5.2 (VSS), J3.6, J4.4
I2C1_SCL: J3.2, J4.2
I2C1_SDA: J3.1, J4.1
LED_DATA_IN: D4.3 (DIN), J3.4
MainBTN: J3.3, SW3.2
unnamed: D4.1 (DOUT), D5.3 (DIN)

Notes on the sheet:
découplage local
LED Adressables
Bouton de commande
LEDs Commandables
Connecteurs LED + Bouton + Ecran

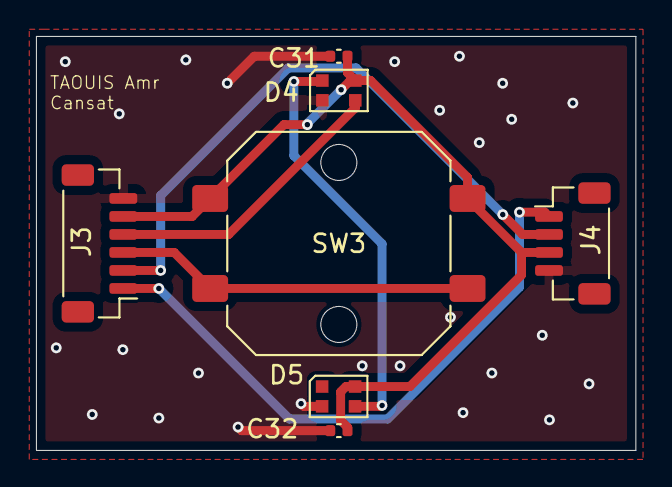
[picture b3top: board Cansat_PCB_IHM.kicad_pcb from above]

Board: 2 copper layers, 33.3 x 23.0 mm, 7 parts (0 on the bottom side), 7 nets.

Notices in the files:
README.md:
License: Educational
